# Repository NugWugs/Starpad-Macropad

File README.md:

## Components:
- 4x2 Macropad Layout
- 1 Encoder Switch
- 1 0.91" 128x32 OLED Display
- Seeed Studio XIAO RP2040

## Function:
- Keys are programmed to hotkeys for different purposes
- Rotation of encoder changes volume
- Pressing of encoder switches between sets of hotkeys
- OLED displays selected hotkey set

## Onshape Link (CAD): 
https://cad.onshape.com/documents/8be66bb81c9edfabe40a1824/w/8ff97f5b07f3c9e6564f80fb/e/1183bdaa753b085b3b18a6f9?renderMode=0&uiState=6a6c30bb5d9455abadad6628

## CAD:

## PCB:

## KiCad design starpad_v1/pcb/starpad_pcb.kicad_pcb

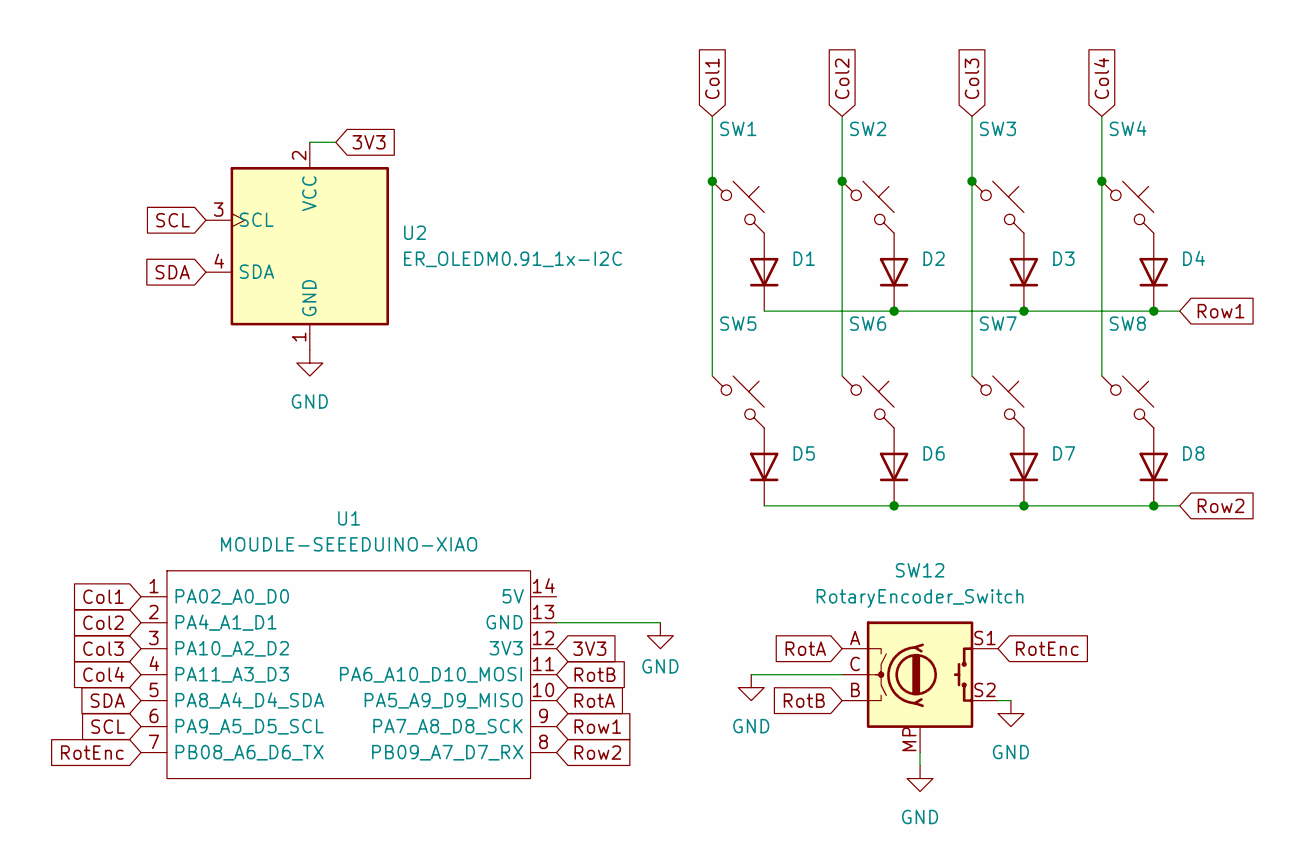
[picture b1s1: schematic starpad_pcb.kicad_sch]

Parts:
D1, D2, D3, D4, D5, D6, D7, D8: 1N914; D_DO-35_SOD27_P7.62mm_Horizontal
SW1, SW2, SW3, SW4, SW5, SW6, SW7, SW8: SW_Push_45deg; MX_PCB_1.00u
SW12: RotaryEncoder_Switch; RotaryEncoder_Alps_EC11E-Switch_Vertical_H20mm
U1: MOUDLE-SEEEDUINO-XIAO; XIAO-Generic-Hybrid-14P-2.54-21X17.8MM
U2: ER_OLEDM0.91_1x-I2C; SSD1306-0.91-OLED-4pin-128x32

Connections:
3V3: U1.12 (3V3), U2.2 (VCC)
Col1: SW1.1, SW5.1, U1.1 (PA02_A0_D0)
Col2: SW2.1, SW6.1, U1.2 (PA4_A1_D1)
Col3: SW3.1, SW7.1, U1.3 (PA10_A2_D2)
Col4: SW4.1, SW8.1, U1.4 (PA11_A3_D3)
GND: SW12.C, SW12.MP, SW12.S2, U1.13 (GND), U2.1 (GND)
unnamed: D1.2 (A), SW1.2
unnamed: D2.2 (A), SW2.2
unnamed: D3.2 (A), SW3.2
unnamed: D4.2 (A), SW4.2
unnamed: D5.2 (A), SW5.2
unnamed: D6.2 (A), SW6.2
unnamed: D7.2 (A), SW7.2
unnamed: D8.2 (A), SW8.2
RotA: SW12.A, U1.10 (PA5_A9_D9_MISO)
RotB: SW12.B, U1.11 (PA6_A10_D10_MOSI)
RotEnc: SW12.S1, U1.7 (PB08_A6_D6_TX)
Row1: D1.1 (K), D2.1 (K), D3.1 (K), D4.1 (K), U1.9 (PA7_A8_D8_SCK)
Row2: D5.1 (K), D6.1 (K), D7.1 (K), D8.1 (K), U1.8 (PB09_A7_D7_RX)
SCL: U1.6 (PA9_A5_D5_SCL), U2.3 (SCL)
SDA: U1.5 (PA8_A4_D4_SDA), U2.4 (SDA)

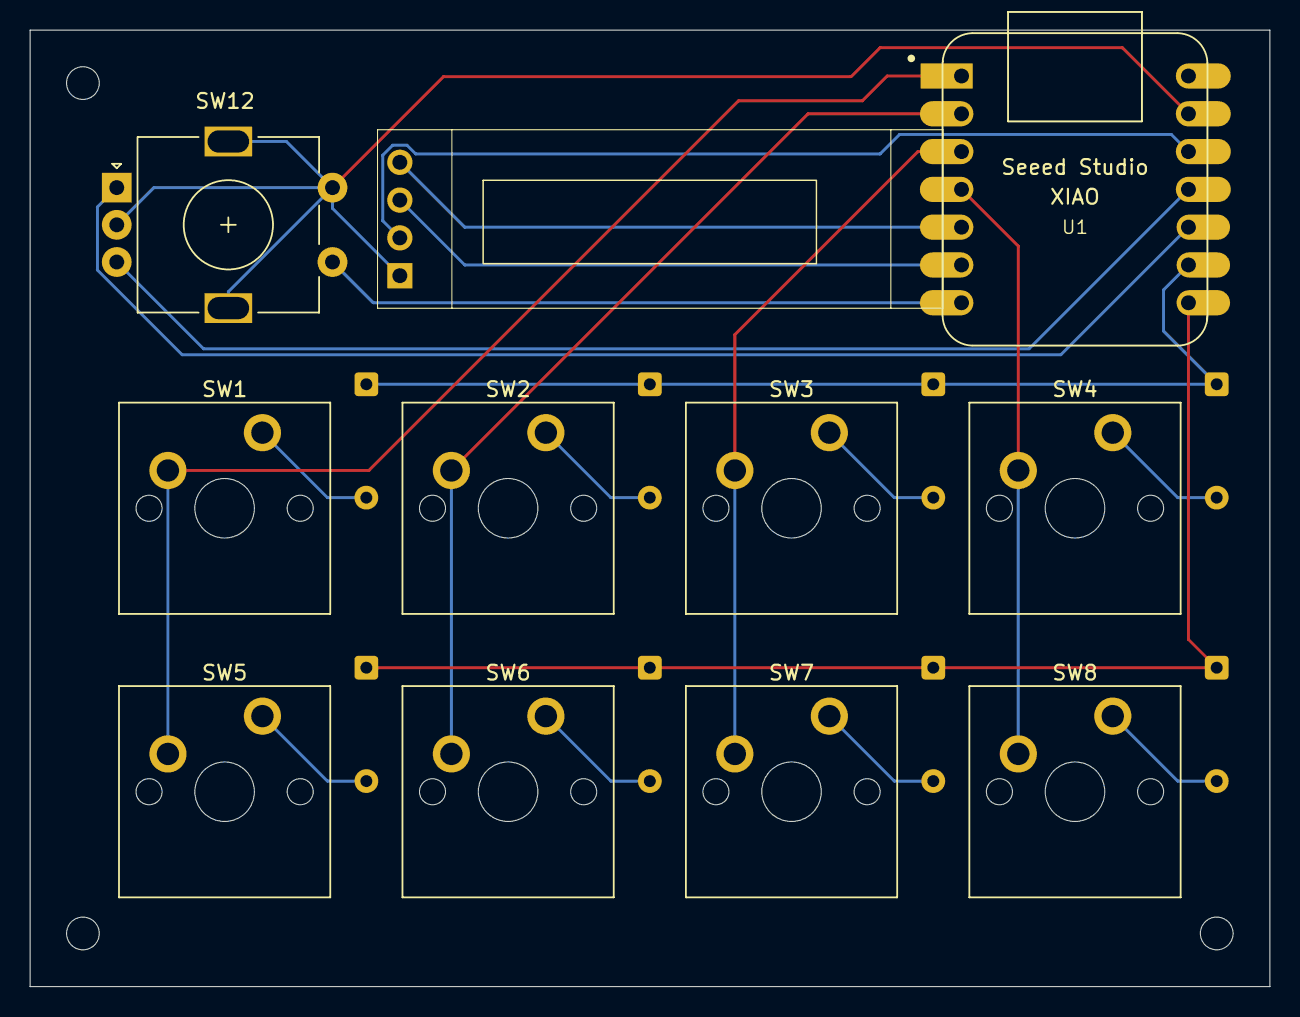
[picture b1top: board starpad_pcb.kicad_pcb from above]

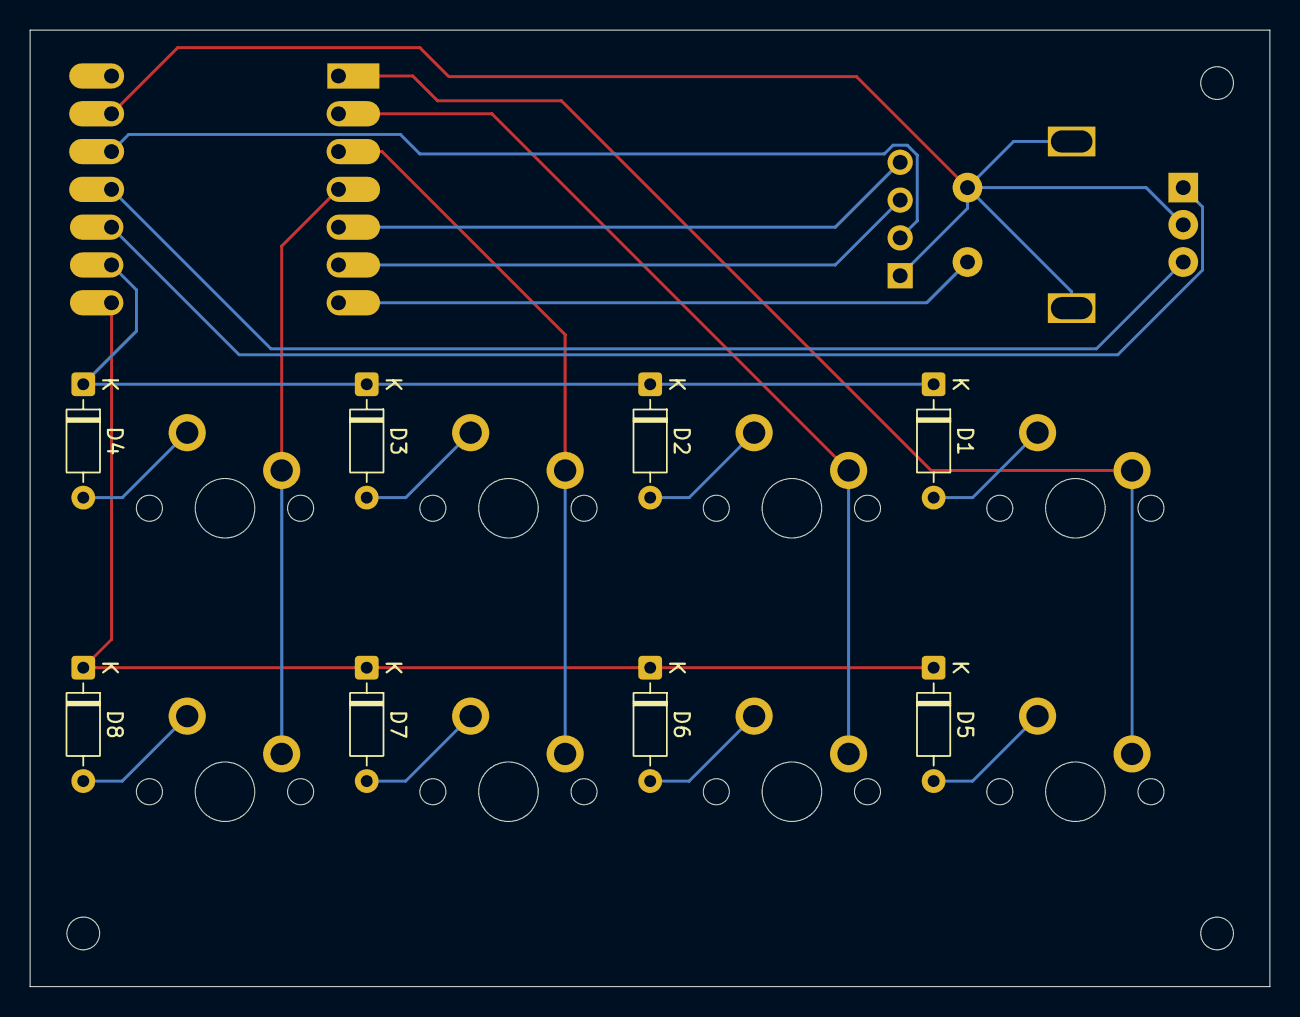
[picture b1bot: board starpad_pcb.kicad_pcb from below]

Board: 2 copper layers, 83.3 x 64.3 mm, 19 parts (8 on the bottom side), 21 nets.
